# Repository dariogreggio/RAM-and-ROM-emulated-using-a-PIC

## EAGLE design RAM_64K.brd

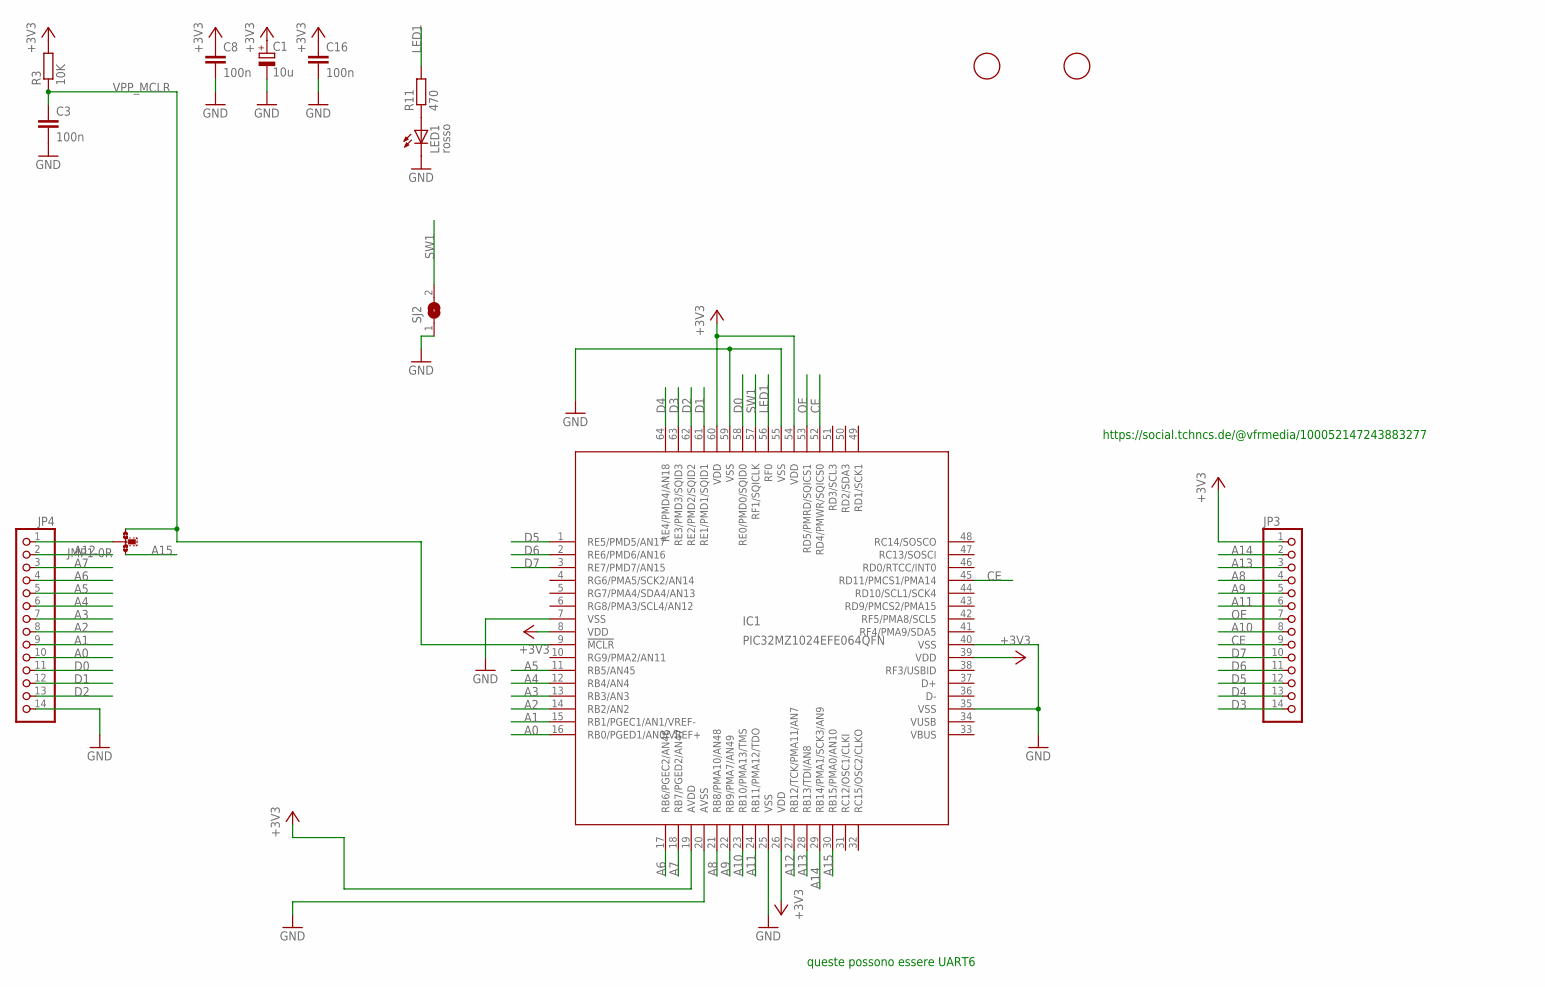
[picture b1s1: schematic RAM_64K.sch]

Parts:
C1: 10u; SMC_B
C3, C8, C16: 100n; C0805
F1, F2: FIDUCIAL; FIDUCIAL_1MM
IC1: PIC32MZ1024EFE064QFN; QFN64
JMP1: 0R-JUMPC; C0R-JMP
JP3, JP4: PINHD-1X14_2.54; 1X14
LED1: rosso; CHIPLED_0805
R3: 10K; R0805
R11: 470; R0805
SJ2: SJ

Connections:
+3V3: C1.+, C8.1, C16.1, IC1.8 (VDD), IC1.19 (AVDD), IC1.26 (VDD), IC1.39 (VDD), IC1.54 (VDD), IC1.60 (VDD), JP3.1, R3.2
A0: IC1.16 (RB0/PGED1/AN0/VREF+), JP4.10
A1: IC1.15 (RB1/PGEC1/AN1/VREF-), JP4.9
A2: IC1.14 (RB2/AN2), JP4.8
A3: IC1.13 (RB3/AN3), JP4.7
A4: IC1.12 (RB4/AN4), JP4.6
A5: IC1.11 (RB5/AN45), JP4.5
A6: IC1.17 (RB6/PGEC2/AN46), JP4.4
A7: IC1.18 (RB7/PGED2/AN47), JP4.3
A8: IC1.21 (RB8/PMA10/AN48), JP3.4
A9: IC1.22 (RB9/PMA7/AN49), JP3.5
A10: IC1.23 (RB10/PMA13/TMS), JP3.8
A11: IC1.24 (RB11/PMA12/TDO), JP3.6
A12: IC1.27 (RB12/TCK/PMA11/AN7), JP4.2
A13: IC1.28 (RB13/TDI/AN8), JP3.3
A14: IC1.29 (RB14/PMA1/SCK3/AN9), JP3.2
A15: IC1.30 (RB15/PMA0/AN10), JMP1.1
CE: IC1.45 (RD11/PMCS1/PMA14), IC1.52 (RD4/PMWR/SQICS0), JP3.9
D0: IC1.58 (RE0/PMD0/SQID0), JP4.11
D1: IC1.61 (RE1/PMD1/SQID1), JP4.12
D2: IC1.62 (RE2/PMD2/SQID2), JP4.13
D3: IC1.63 (RE3/PMD3/SQID3), JP3.14
D4: IC1.64 (RE4/PMD4/AN18), JP3.13
D5: IC1.1 (RE5/PMD5/AN17), JP3.12
D6: IC1.2 (RE6/PMD6/AN16), JP3.11
D7: IC1.3 (RE7/PMD7/AN15), JP3.10
GND: C1.-, C3.2, C8.2, C16.2, IC1.7 (VSS), IC1.20 (AVSS), IC1.25 (VSS), IC1.35 (VSS), IC1.40 (VSS), IC1.55 (VSS), IC1.59 (VSS), JP4.14, LED1.C, SJ2.1
LED1: IC1.56 (RF0), R11.2
unnamed: JMP1.2, JP4.1
unnamed: LED1.A, R11.1
OE: IC1.53 (RD5/PMRD/SQICS1), JP3.7
SW1: IC1.57 (RF1/SQICLK), SJ2.2
VPP_MCLR: C3.1, IC1.9 (!MCLR), JMP1.3, R3.1
VUSB: IC1.34 (VUSB)

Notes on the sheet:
queste possono essere UART6
https://social.tchncs.de/@vfrmedia/100052147243883277

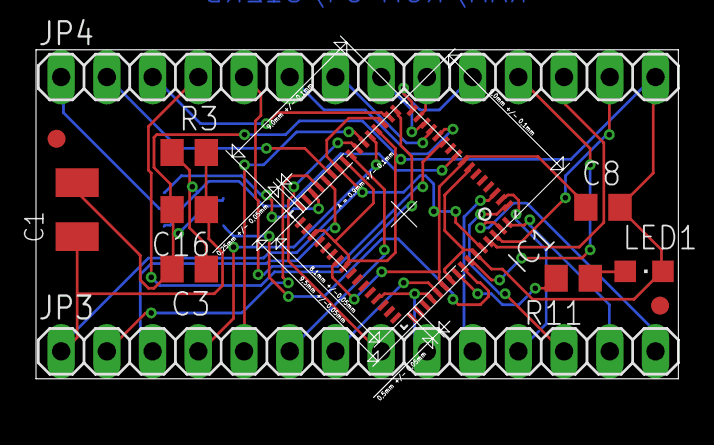
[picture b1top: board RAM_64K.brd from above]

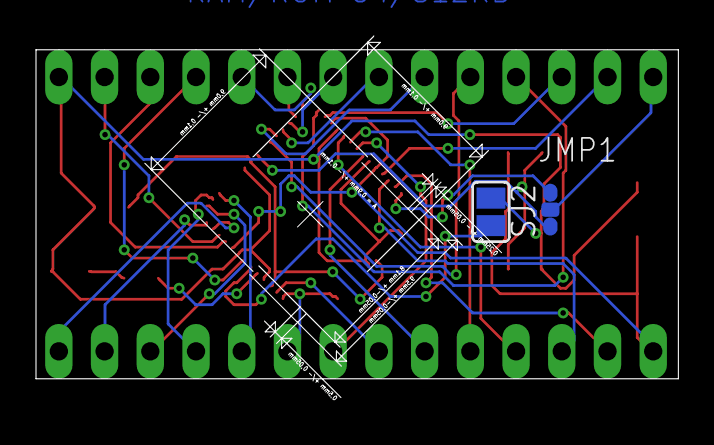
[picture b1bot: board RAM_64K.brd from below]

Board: 2 copper layers, 35.7 x 20.7 mm, 14 parts (2 on the bottom side), 33 nets.

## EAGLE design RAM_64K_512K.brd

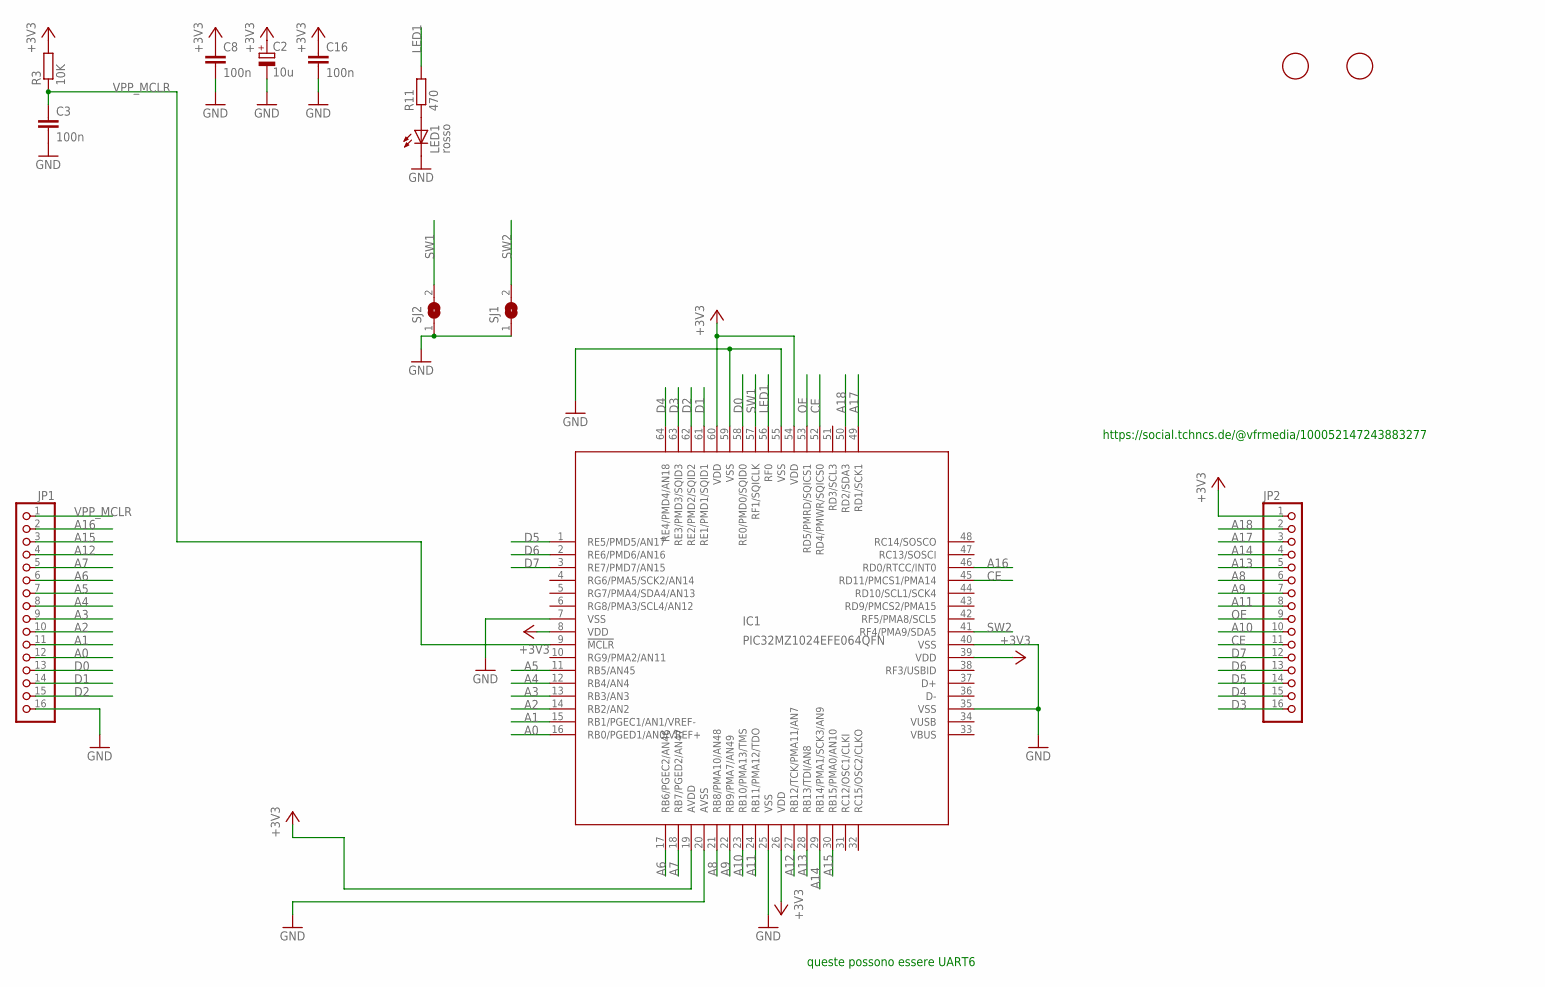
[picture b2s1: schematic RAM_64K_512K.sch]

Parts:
C2: 10u; SMC_B
C3, C8, C16: 100n; C0805
F1, F2: FIDUCIAL; FIDUCIAL_1MM
IC1: PIC32MZ1024EFE064QFN; QFN64
JP1, JP2: PINHD-1X16_2.54; 1X16
LED1: rosso; CHIPLED_0805
R3: 10K; R0805
R11: 470; R0805
SJ1, SJ2: SJ

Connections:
+3V3: C2.+, C8.1, C16.1, IC1.8 (VDD), IC1.19 (AVDD), IC1.26 (VDD), IC1.39 (VDD), IC1.54 (VDD), IC1.60 (VDD), JP2.1, R3.2
A0: IC1.16 (RB0/PGED1/AN0/VREF+), JP1.12
A1: IC1.15 (RB1/PGEC1/AN1/VREF-), JP1.11
A2: IC1.14 (RB2/AN2), JP1.10
A3: IC1.13 (RB3/AN3), JP1.9
A4: IC1.12 (RB4/AN4), JP1.8
A5: IC1.11 (RB5/AN45), JP1.7
A6: IC1.17 (RB6/PGEC2/AN46), JP1.6
A7: IC1.18 (RB7/PGED2/AN47), JP1.5
A8: IC1.21 (RB8/PMA10/AN48), JP2.6
A9: IC1.22 (RB9/PMA7/AN49), JP2.7
A10: IC1.23 (RB10/PMA13/TMS), JP2.10
A11: IC1.24 (RB11/PMA12/TDO), JP2.8
A12: IC1.27 (RB12/TCK/PMA11/AN7), JP1.4
A13: IC1.28 (RB13/TDI/AN8), JP2.5
A14: IC1.29 (RB14/PMA1/SCK3/AN9), JP2.4
A15: IC1.30 (RB15/PMA0/AN10), JP1.3
A16: IC1.46 (RD0/RTCC/INT0), JP1.2
A17: IC1.49 (RD1/SCK1), JP2.3
A18: IC1.50 (RD2/SDA3), JP2.2
CE: IC1.45 (RD11/PMCS1/PMA14), IC1.52 (RD4/PMWR/SQICS0), JP2.11
D0: IC1.58 (RE0/PMD0/SQID0), JP1.13
D1: IC1.61 (RE1/PMD1/SQID1), JP1.14
D2: IC1.62 (RE2/PMD2/SQID2), JP1.15
D3: IC1.63 (RE3/PMD3/SQID3), JP2.16
D4: IC1.64 (RE4/PMD4/AN18), JP2.15
D5: IC1.1 (RE5/PMD5/AN17), JP2.14
D6: IC1.2 (RE6/PMD6/AN16), JP2.13
D7: IC1.3 (RE7/PMD7/AN15), JP2.12
GND: C2.-, C3.2, C8.2, C16.2, IC1.7 (VSS), IC1.20 (AVSS), IC1.25 (VSS), IC1.35 (VSS), IC1.40 (VSS), IC1.55 (VSS), IC1.59 (VSS), JP1.16, LED1.C, SJ1.1, SJ2.1
LED1: IC1.56 (RF0), R11.2
unnamed: LED1.A, R11.1
OE: IC1.53 (RD5/PMRD/SQICS1), JP2.9
SW1: IC1.57 (RF1/SQICLK), SJ2.2
SW2: IC1.41 (RF4/PMA9/SDA5), SJ1.2
VPP_MCLR: C3.1, IC1.9 (!MCLR), JP1.1, R3.1
VUSB: IC1.34 (VUSB)

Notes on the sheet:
queste possono essere UART6
https://social.tchncs.de/@vfrmedia/100052147243883277

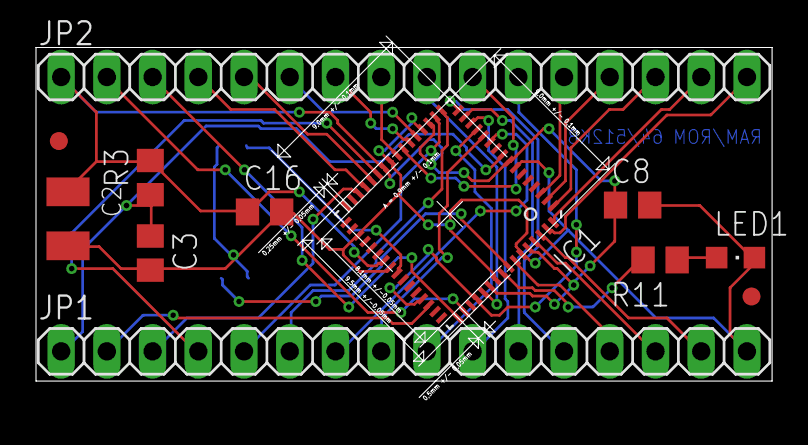
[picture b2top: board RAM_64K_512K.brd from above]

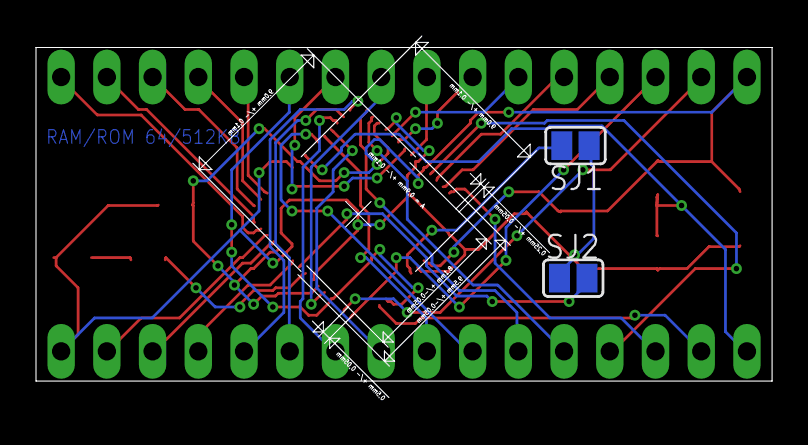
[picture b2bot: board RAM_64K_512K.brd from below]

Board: 2 copper layers, 40.9 x 20.7 mm, 14 parts (2 on the bottom side), 36 nets.
